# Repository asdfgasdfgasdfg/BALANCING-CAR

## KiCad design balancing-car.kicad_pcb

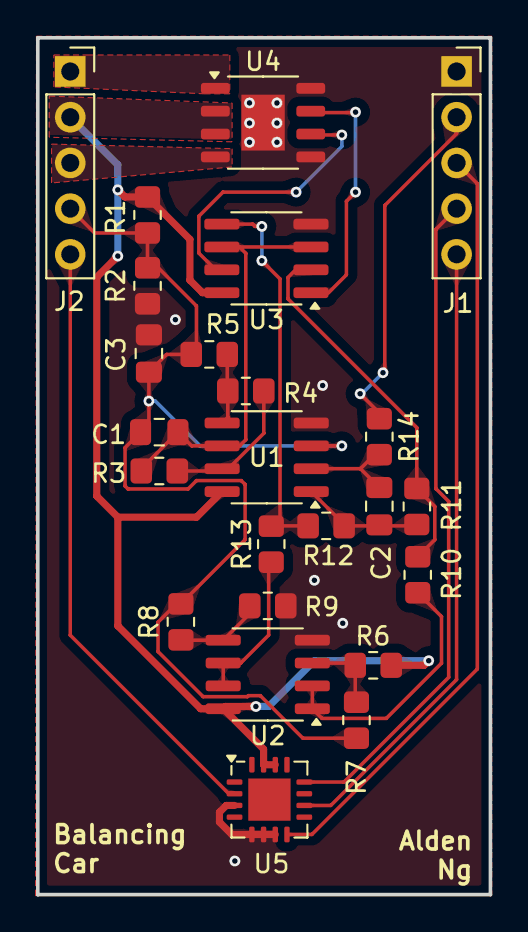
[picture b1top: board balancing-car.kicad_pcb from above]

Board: 2 copper layers, 25.1 x 47.6 mm, 24 parts (0 on the bottom side), 23 nets.

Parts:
C1: 10nF; C_0805_2012Metric_Pad1.18x1.45mm_HandSolder
C2, C3: 1uF; C_0805_2012Metric_Pad1.18x1.45mm_HandSolder
J1, J2: Conn_01x05_Socket; PinSocket_1x05_P2.54mm_Vertical
R1, R2: 10k; R_0805_2012Metric_Pad1.20x1.40mm_HandSolder
R3, R14: 100k; R_0805_2012Metric_Pad1.20x1.40mm_HandSolder
R4: 82k; R_0805_2012Metric_Pad1.20x1.40mm_HandSolder
R5, R7, R8: 20k; R_0805_2012Metric_Pad1.20x1.40mm_HandSolder
R6, R9: 24k; R_0805_2012Metric_Pad1.20x1.40mm_HandSolder
R10, R13: 43k; R_0805_2012Metric_Pad1.20x1.40mm_HandSolder
R11, R12: 47k; R_0805_2012Metric_Pad1.20x1.40mm_HandSolder
U1, U2, U3: MCP602; SOIC-8_3.9x4.9mm_P1.27mm
U4: L9110h; HSOP-8-1EP_3.9x4.9mm_P1.27mm_EP2.41x3.1mm
U5: ADXL335; Analog_LFCSP-16-1EP_4x4mm_P0.65mm_EP2.35x2.35mm

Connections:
/Acceleration: J1.2, R14.1
/MotorA: J2.1, U4.1 (OutA)
/MotorB: J2.3, U4.4 (OutB)
/ST: J2.5, U5.2 (ST)
/Vmid: C1.1, C3.2, J2.4, R1.2, R2.1, R5.2, R7.2, R8.1, U1.3 (+)
/Xout: J1.4, U5.12 (Xout)
/Yout: J1.5, U5.10 (Yout)
/Zout: J1.3, U5.8 (Zout)
/v_sharktooth: C1.2, R3.1, U1.6 (-), U3.3 (+), U3.6 (-)
/velocity: C2.2, R11.1, R12.2, U1.1
GND: C3.1, J1.1, R2.2, R9.2, U1.4 (V-), U2.4 (V-), U3.4 (V-), U4.5 (V-), U4.8 (V-), U4.9, U5.3 (Gnd), U5.5 (Gnd), U5.6 (Gnd), U5.7 (Gnd)
unnamed: R3.2, R4.1, U1.7
unnamed: C2.1, R14.2, U1.2 (-)
unnamed: R4.2, R5.1, U1.5 (+)
unnamed: R6.2, R7.1, U2.3 (+)
unnamed: R10.1, U2.1, U2.2 (-)
unnamed: R8.2, R9.1, U2.5 (+)
unnamed: R13.1, U2.6 (-), U2.7
unnamed: R10.2, R11.2, U3.2 (-)
unnamed: R12.1, R13.2, U3.5 (+)
unnamed: U3.7, U4.6 (InA)
unnamed: U3.1, U4.7 (InB)
VCC: J2.2, R1.1, R6.1, U1.8 (V+), U2.8 (V+), U3.8 (V+), U4.2 (V+), U4.3 (V+), U5.14 (Vcc), U5.15 (Vcc)

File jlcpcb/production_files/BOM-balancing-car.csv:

Comment,Designator,Footprint,LCSC,Quantity
100k,"R14,R3",R_0805_2012Metric_Pad1.20x1.40mm_HandSolder,C149504,2
10nF,C1,C_0805_2012Metric_Pad1.18x1.45mm_HandSolder,C1710,1
10k,"R1,R2",R_0805_2012Metric_Pad1.20x1.40mm_HandSolder,C17414,2
24k,"R6,R9",R_0805_2012Metric_Pad1.20x1.40mm_HandSolder,C17575,2
43k,"R10,R13",R_0805_2012Metric_Pad1.20x1.40mm_HandSolder,C17695,2
47k,"R11,R12",R_0805_2012Metric_Pad1.20x1.40mm_HandSolder,C17713,2
82k,R4,R_0805_2012Metric_Pad1.20x1.40mm_HandSolder,C17840,1
1uF,"C2,C3",C_0805_2012Metric_Pad1.18x1.45mm_HandSolder,C28323,2
MCP602,"U1,U2,U3",SOIC-8_3.9x4.9mm_P1.27mm,C29605,3
ADXL335,U5,Analog_LFCSP-16-1EP_4x4mm_P0.65mm_EP2.35x2.35mm,C34439,1
20k,"R5,R7,R8",R_0805_2012Metric_Pad1.20x1.40mm_HandSolder,C4328,3
L9110h,U4,HSOP-8-1EP_3.9x4.9mm_P1.27mm_EP2.41x3.1mm,C513306,1
Conn_01x05_Socket,J1,PinSocket_1x05_P2.54mm_Vertical,,1
Conn_01x05_Socket,J2,PinSocket_1x05_P2.54mm_Vertical,,1
